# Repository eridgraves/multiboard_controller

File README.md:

# multiboard-controller
A board to connect a single host to multiple dev/eval boards, each with:
- Power over USB
- USB (shared with above?) for Fastboot communication 
- Serial (RS-232)

Only one board can be active at a time.  The current board can be selected using a [switch/microcontroller]? and is displayed on a [screen/LEDs]?.

Currently, the chip select output is handled by a 3 bit address (3 slide-switches) and submitted using a single toggle switch.

The idea is that this board gives a clean interface between my host PC and full rack of microcontrollers/SoMs without fiddling with wires.

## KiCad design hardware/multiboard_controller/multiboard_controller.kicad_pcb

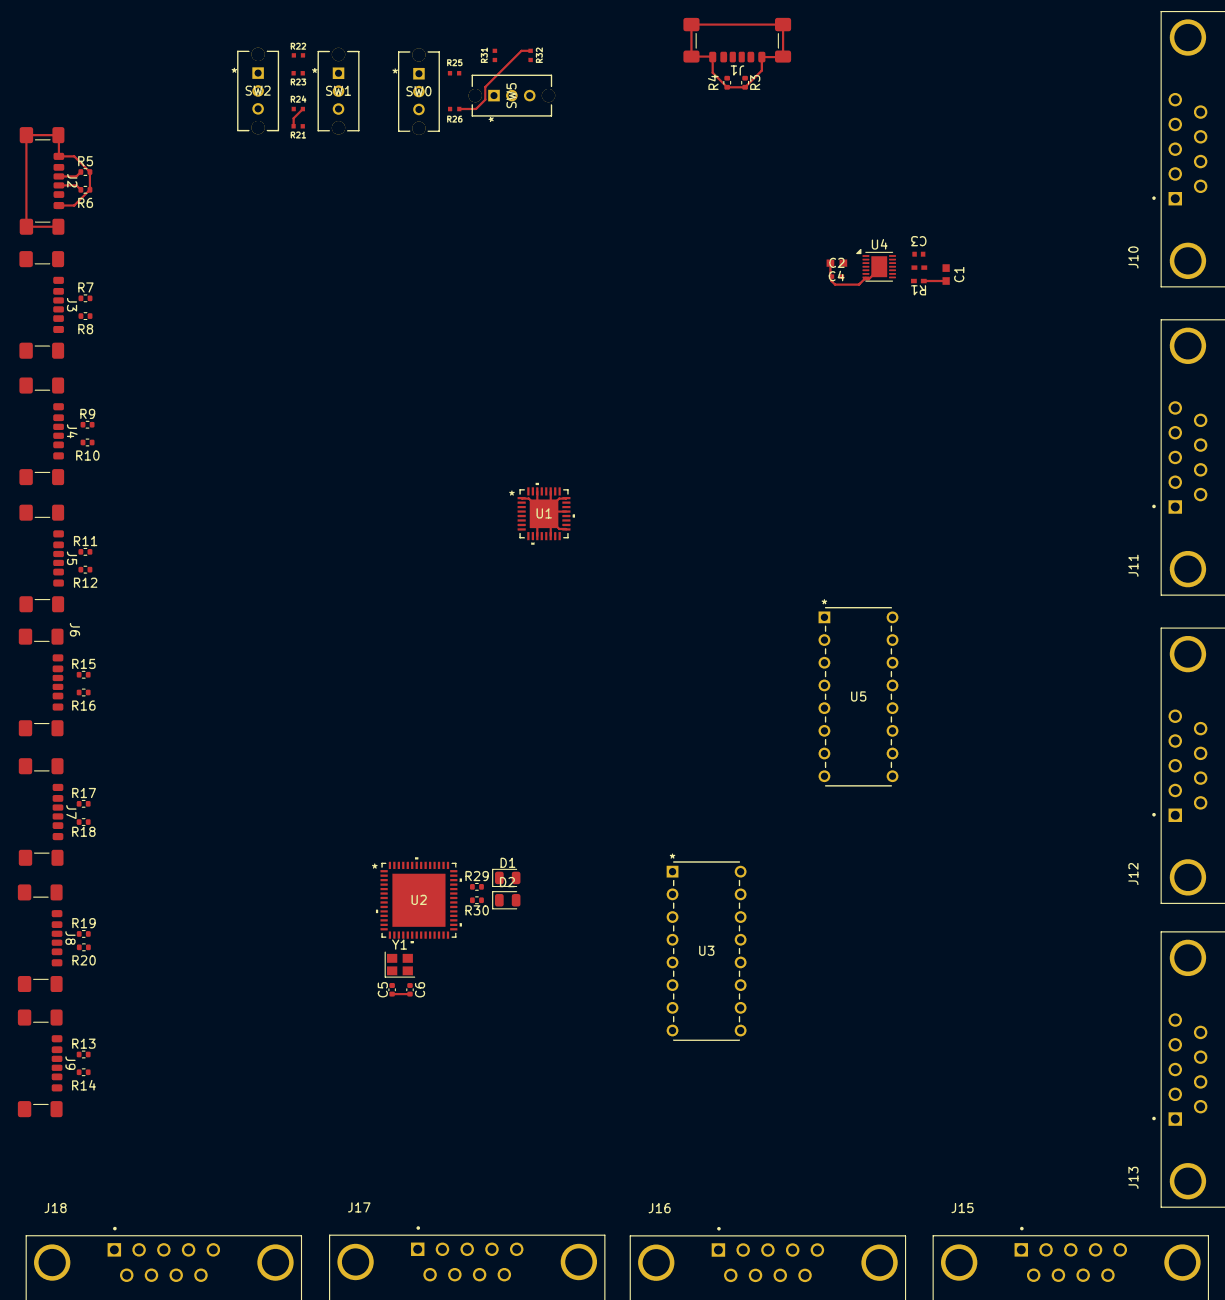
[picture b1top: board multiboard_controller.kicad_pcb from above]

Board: 4 copper layers, 65 parts (0 on the bottom side), 61 nets.

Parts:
C1, C2: 22uF; G-188_MUR
C3: 47nF; CAPC10555_55N_KEM
C4: 1uF; CAP_CL05_SAM
C5, C6: 18pF; C_0402_1005Metric
D1: TXLED; LED_0805_2012Metric
D2: RXLED; LED_0805_2012Metric
J1, J2, J3, J4, J5, J6, J7, J8, J9: USB_C_Receptacle; USB_C_Receptacle_GCT_USB4135-GF-A_6P_TopMnt_Horizontal
J10, J11, J12, J13, J15, J16, J17, J18: DE9_Plug_MountingHoles; ASSMANN_A-DS_09_A_KG-T2S
R1: 15K; RC0402N_PAN
R2: 68.1K; RC0402N_PAN
R3, R4, R5, R6, R7, R8, R9, R10, R11, R12, R13, R14, R15, R16, R17, R18, R19, R20: 5.1K; R_0402_1005Metric
R21, R22, R23, R24, R25, R26, R31, R32: 10K; RES_ERJ2RKF1002X
R29, R30: 220; R_0402_1005Metric
SW0, SW1, SW2, SW5: OS102011MS2QN1; SPDT_OS102011_CNK
U1: max4999etj+; 21-0140_T3255&plus_4_MXM-M
U2: FT232HPQ-TRAY; QFN-56_FT232HPQ_FTD
U3, U5: DG408DJZ; PDIP16_E16.3_REN
U4: MAX38908xTD; TDFN-14-1EP_3x3mm_P0.4mm_EP1.78x2.35mm
Y1: 12MHz; Crystal_SMD_2520-4Pin_2.5x2.0mm

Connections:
+3V3: C1.2, C3.2, D1.2 (A), D2.2 (A), R2.1, R22.2, R23.2, R25.2, R31.2, U1.2 (VCC), U1.20 (VCC), U2.5 (VCCIO), U2.13 (VCCIO), U2.14 (VCCIO), U2.18 (VREGIN), U2.28 (VCCIO), U2.40 (VCCIO), U4.11 (OUT), U4.12 (OUT), U4.13 (OUT), U4.14 (OUT)
/Serial/RXD: U2.24 (ADBUS1), U5.8 (D)
/Serial/TXD: U2.23 (ADBUS0), U3.8 (D)
/Serial/VREGOUT: U2.11 (VCORE), U2.19 (VREGOUT), U2.22 (VCORE), U2.36 (VCORE), U2.46 (VCORE), U2.56 (VCORE)
C0: SW0.2, U1.6 (C0), U3.1 (A0), U5.1 (A0)
C1: SW1.2, U1.7 (C1), U3.16 (A1), U5.16 (A1)
C2: SW2.2, U1.8 (C2), U3.15 (A2), U5.15 (A2)
CH_EN: SW5.2, U1.3 (EN), U3.2 (EN), U5.2 (EN)
DE9_0_GND: C1.1, C2.1, C4.1, C5.2, C6.2, J1.A12 (GND), J1.B12 (GND), J1.S1 (SHIELD), J2.A12 (GND), J2.B12 (GND), J2.S1 (SHIELD), J3.A12 (GND), J3.B12 (GND), J3.S1 (SHIELD), J4.A12 (GND), J4.B12 (GND), J4.S1 (SHIELD), J5.A12 (GND), J5.B12 (GND), J5.S1 (SHIELD), J6.A12 (GND), J6.B12 (GND), J6.S1 (SHIELD), J7.A12 (GND), J7.B12 (GND), J7.S1 (SHIELD), J8.A12 (GND), J8.B12 (GND), J8.S1 (SHIELD), J9.A12 (GND), J9.B12 (GND), J9.S1 (SHIELD), J10.5, J11.5, J12.5, J13.5, J15.5, J16.5, J17.5, J18.5, R1.2, R3.2, R4.2, R5.2, R6.2, R7.2, R8.2, R9.2, R10.2, R11.2, R12.2, R13.2, R14.2, R15.2, R16.2, R17.2, R18.2, R19.2, R20.2, R21.1, R24.1, R26.1, R32.1, U1.1 (GND), U1.11 (GND), U1.14 (GND), U1.17 (GND), U1.21 (GND), U1.24 (GND), U1.27 (GND), U1.30 (GND), U1.33 (EPAD), U2.4 (TEST), U2.12 (GND), U2.17 (GND), U2.41 (GND), U2.57 (GGND), U3.3 (V-), U3.14 (GND), U4.7 (GND), U4.15 (GND), U5.3 (V-), U5.14 (GND)
DE9_0_RX: J10.2, U5.4 (S1)
DE9_0_TX: J10.3, U3.4 (S1)
DE9_1_RX: J11.2, U5.5 (S2)
DE9_1_TX: J11.3, U3.5 (S2)
DE9_2_RX: J12.2, U5.6 (S3)
DE9_2_TX: J12.3, U3.6 (S3)
DE9_3_RX: J13.2, U5.7 (S4)
DE9_3_TX: J13.3, U3.7 (S4)
DE9_4_RX: J15.2, U5.12 (S5)
DE9_4_TX: J15.3, U3.12 (S5)
DE9_5_RX: J16.2, U5.11 (S6)
DE9_5_TX: J16.3, U3.11 (S6)
DE9_6_RX: J17.2, U5.10 (S7)
DE9_6_TX: J17.3, U3.10 (S7)
DE9_7_RX: J18.2, U5.9 (S8)
DE9_7_TX: J18.3, U3.9 (S8)
unnamed: D1.1 (K), R29.1
unnamed: D2.1 (K), R30.1
unnamed: J1.A5 (CC1), R3.1
unnamed: J1.B5 (CC2), R4.1
unnamed: J2.A5 (CC1), R5.1
unnamed: J2.B5 (CC2), R6.1
unnamed: J3.A5 (CC1), R7.1
unnamed: J3.B5 (CC2), R8.1
unnamed: J4.A5 (CC1), R9.1
unnamed: J4.B5 (CC2), R10.1
unnamed: J5.A5 (CC1), R11.1
unnamed: J5.B5 (CC2), R12.1
unnamed: J6.A5 (CC1), R15.1
unnamed: J6.B5 (CC2), R16.1
unnamed: J7.A5 (CC1), R17.1
unnamed: J7.B5 (CC2), R18.1
unnamed: J8.A5 (CC1), R19.1
unnamed: J8.B5 (CC2), R20.1
unnamed: J9.A5 (CC1), R13.1
unnamed: J9.B5 (CC2), R14.1
unnamed: R21.2, SW1.3
unnamed: R22.1, SW1.1
unnamed: R23.1, SW2.1
unnamed: R24.2, SW2.3
unnamed: R25.1, SW0.1
unnamed: R26.2, SW0.3
unnamed: R31.1, SW5.1
unnamed: R32.2, SW5.3
unnamed: R30.2, U2.35 (ACBUS3)
unnamed: R29.2, U2.37 (ACBUS4)
unnamed: C5.1, U2.15 (OSCI), Y1.1
unnamed: C6.1, U2.16 (OSCO), Y1.2
unnamed: C4.2, U4.5 (BIAS), U4.6 (EN)
unnamed: C3.1, U4.10 (BYP)
unnamed: R1.1, R2.2, U4.9 (FB)
V_BUS: C2.2, J1.A9 (VBUS), J1.B9 (VBUS), J2.A9 (VBUS), J2.B9 (VBUS), J3.A9 (VBUS), J3.B9 (VBUS), J4.A9 (VBUS), J4.B9 (VBUS), J5.A9 (VBUS), J5.B9 (VBUS), J6.A9 (VBUS), J6.B9 (VBUS), J7.A9 (VBUS), J7.B9 (VBUS), J8.A9 (VBUS), J8.B9 (VBUS), J9.A9 (VBUS), J9.B9 (VBUS), U3.13 (V+), U4.1 (IN), U4.2 (IN), U4.3 (IN), U4.4 (IN), U5.13 (V+)

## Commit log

2025-02-11 Adding initial project structure, block diagram, and WIP USB-chip schematic.
2025-02-12 Adding USB Connector for Power and Data
    First USB connector is for power and data input from the host. Power is taken from the V_BUS line and stepped to 3V3 to power other components using an LDO. Updated block diagram accordingly.
2025-02-13 Add Channel Select switches and USB output ports
2025-02-13 Add TODO
2025-02-14 Creating serial outputs.
2025-02-16 Choose switches for UART muxing. USB-to-UART schematic WIP.
2025-02-17 Connecting first UART line out from mux
2025-02-18 Full USB-to-UART connections
    - Connect switches and convertor IC in USB-UART mode
    - Change CH_EN input signal from momentary button to switch to work with
    switch chips (since it expects high enable to output signal)
    TODOs:
    - Confirm that resistors built into ICs are enough to protect USB/UART
    signals.
2025-02-20 Adding changes before rearch to usb controller hub
2025-02-22 Create new branch for usb hub -based design
2025-03-03 Adding final connectors and general cleanup.
2025-03-04 Starting layout
    Add serial ground connections, add footprint libraries, start layout.
2025-03-05 Updating connections to USB output connectors, prepped subsystems for board layout.
2025-03-05 Man I have no idea how to layout a board
